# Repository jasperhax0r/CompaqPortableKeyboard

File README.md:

# Compaq Portable Keyboard — Replacement PCB, Firmware & Protocol

A drop-in replacement keyboard controller for the **Compaq Portable** (1983),
built around a Raspberry Pi Pico. It reads an 83-key diode matrix and speaks the
machine's native **IBM XT (scancode set 1)** protocol over the original 2×3
keyboard connector.

The repo also contains a **USB-serial / PS-2 test rig** used during bring-up, and
— probably the most useful part for other people — a **scope-verified writeup of
the Compaq Portable keyboard protocol**, which as far as I can tell isn't
documented anywhere else public.

Everything here is hand-solderable through-hole where possible, on purpose. The
only surface-mount parts are the two level-shifter buffers, and even those have a
through-hole alternative described in the build notes.

---

## Why this exists

The original keyboard PCBs are getting old, and the matrix routing on the
factory board is... a journey. This recreates the keyboard's electrical behavior
faithfully enough that the machine POSTs and types exactly as it did in 1983,
while letting you rebuild the board with a $15 iron and a solder sucker.

The first PCB revision is a **faithful recreation** of the original layout, on
purpose — it's a known-good reference. A rev2 with layout improvements is planned
(see `docs/rev2-notes.md`).

---

## Repository layout

```
/firmware        Pico firmware (CircuitPython)
  code.py          matrix-scan keyboard firmware (the real thing)
  test-rig/        USB-serial + PS-2 bring-up firmware
/hardware        KiCad project, schematic, PCB, Gerbers
/models          3D-printable STLs (connector keyway + fitment shims)
/tools           protocol decoder + KLE matrix-annotation scripts
  xtframe.py       decode a logic-analyzer CSV into XT scancodes
  kle_annotate.py  annotate a raw KLE layout with matrix coordinates
/docs            protocol writeup, build notes, rev2 log
```

---

## How it works

The Pico scans a **10×10 diode matrix** (83 keys, one diode per key, so full
NKRO) and emits XT scancodes on the keyboard connector.

**Power:** the Compaq feeds ~12 V down the cable. An onboard 7805 drops that to
5 V for the buffers, and the Pico runs from that 5 V into VSYS through a Schottky.
The board reproduces the original's protection: reverse-polarity Schottky, a
polyfuse, TVS clamps at the connector, and a 5.6 V crowbar across the 5 V rail.

**Level shifting:** the Pico is 3.3 V and **not** 5 V tolerant. Outbound
clock/data go through an **SN74LVC07A** (open-drain, pulled to 5 V). Inbound
reset and clock-sense come back through an **SN74LVC14A** Schmitt-trigger
cascade — the hysteresis matters, see the protocol notes on line ringing.

**Protocol:** XT scancode set 1. The keyboard generates the clock; each frame is
one start bit plus 8 data bits, LSB first, with data valid on the falling clock
edge, at roughly 24 kHz. On reset release the keyboard waits ~170 ms then sends
`0xAA` (self-test passed). Full details and scope captures in
[`docs/protocol.md`](docs/protocol.md).

---

## Building the firmware

The firmware is **CircuitPython** — no toolchain, no compile step.

1. Flash CircuitPython to the Pico.
2. Copy `firmware/code.py` to the `CIRCUITPY` drive as `code.py`.
3. That's it — it runs on boot.

### Bring-up before you install it

`code.py` has debug switches at the top:

- `DEBUG = True` prints every key make/break to the USB serial console.
- `RAW_SCAN = True` prints the raw `(row, col)` of every press, ignoring the
  keymap — use this to verify your matrix wiring against the board.
- `XT_CONNECTED = False` scans and prints but does **not** drive the XT lines,
  so you can validate the whole matrix over USB with nothing connected to the
  Compaq.

Walk every key with `RAW_SCAN = True` and confirm it matches the board before
trusting the scancode map. When it checks out, set all three back to
`DEBUG = False`, `RAW_SCAN = False`, `XT_CONNECTED = True`.

> **Note on the matrix map:** this board is wired to the *original Compaq's*
> matrix order (a straight sequential fill), **not** the interleaved mapping a
> tool like `kbplacer` produces from the KLE. If you regenerate the keymap from
> the layout file you'll get the wrong table. The map in `code.py` is the
> authoritative one — it was verified key-by-key against the physical board.

---

## Building the board

See [`docs/build.md`](docs/build.md) for the full walkthrough. The short version:

1. **Populate and verify the regulator section first.** Confirm 5.0 V at the rail
   *and* at the buffer VCC pins before any logic sees power.
2. **Power up on a current-limited bench supply** (~150 mA limit) for the first
   power-on. A wiring fault then shows as the supply hitting its limit at ~0 V,
   instead of as a hot regulator and a burn. (Ask me how I know.)
3. Then the Pico, then the level shifters, then the matrix.

The two `SN74LVC0x` buffers are TSSOP — the only fine-pitch parts. Drag-solder
with plenty of flux and wick any bridges. If you'd rather stay all-through-hole,
`docs/build.md` covers a `7407` + `CD4050B` DIP alternative (you lose the Schmitt
hysteresis on the input side, fine for a short cable).

---

## The 3D-printed parts

`/models` has the connector **keyway** (the original connector is mechanically
keyed; the print replicates that so the plug can't seat rotated — important,
since a rotated plug puts 12 V onto a signal line) and **fitment shims**.

Print in any rigid filament. PETG or ABS if it'll sit near the warm regulator;
PLA is fine otherwise.

---

## Tools

`tools/xtframe.py` decodes a logic-analyzer CSV (start bit + 8 data LSB-first,
falling-edge sampled) into XT scancodes, with a `--deglitch-us` option to reject
sub-threshold ringing on a passive tap. It was used to reverse-engineer the
protocol; it's handy for anyone probing an XT-family keyboard.

`tools/kle_annotate.py` annotates a raw [keyboard-layout-editor](https://www.keyboard-layout-editor.com)
JSON with matrix coordinates.

---

## Status

Working. The board POSTs and types on a real Compaq Portable. Known rev1
warts and the planned rev2 fixes are logged in [`docs/rev2-notes.md`](docs/rev2-notes.md)
(regulator thermal pad, hand-solder footprints, silkscreen polarity markers,
axial diode on the 5 V rail, and more).

---

## Licenses

This project is open-source hardware. Different parts carry different licenses,
because software, hardware, and documentation are legally distinct:

| Part | License |
|------|---------|
| Firmware & tools (`/firmware`, `/tools`) | **MIT** |
| Hardware & 3D models (`/hardware`, `/models`) | **CERN-OHL-S v2** |
| Documentation (`/docs`, this README) | **CC-BY-4.0** |

- The **firmware** is MIT — use it however you like.
- The **board and STL designs** are CERN-OHL-S (strongly reciprocal): if you
  make and distribute modified hardware, keep the design files open under the
  same terms.
- The **documentation and protocol writeup** are CC-BY-4.0 — reproduce and build
  on them, with attribution.

Full texts are in `/LICENSES`. See CERN-OHL-S §3 for the source-availability
requirement when distributing hardware based on this design.

---

## Acknowledgements

Original Compaq Portable schematic reference: Howard W. Sams & Co.
Computerfacts, 1987 (used for cross-referencing switch designations during
reverse engineering).

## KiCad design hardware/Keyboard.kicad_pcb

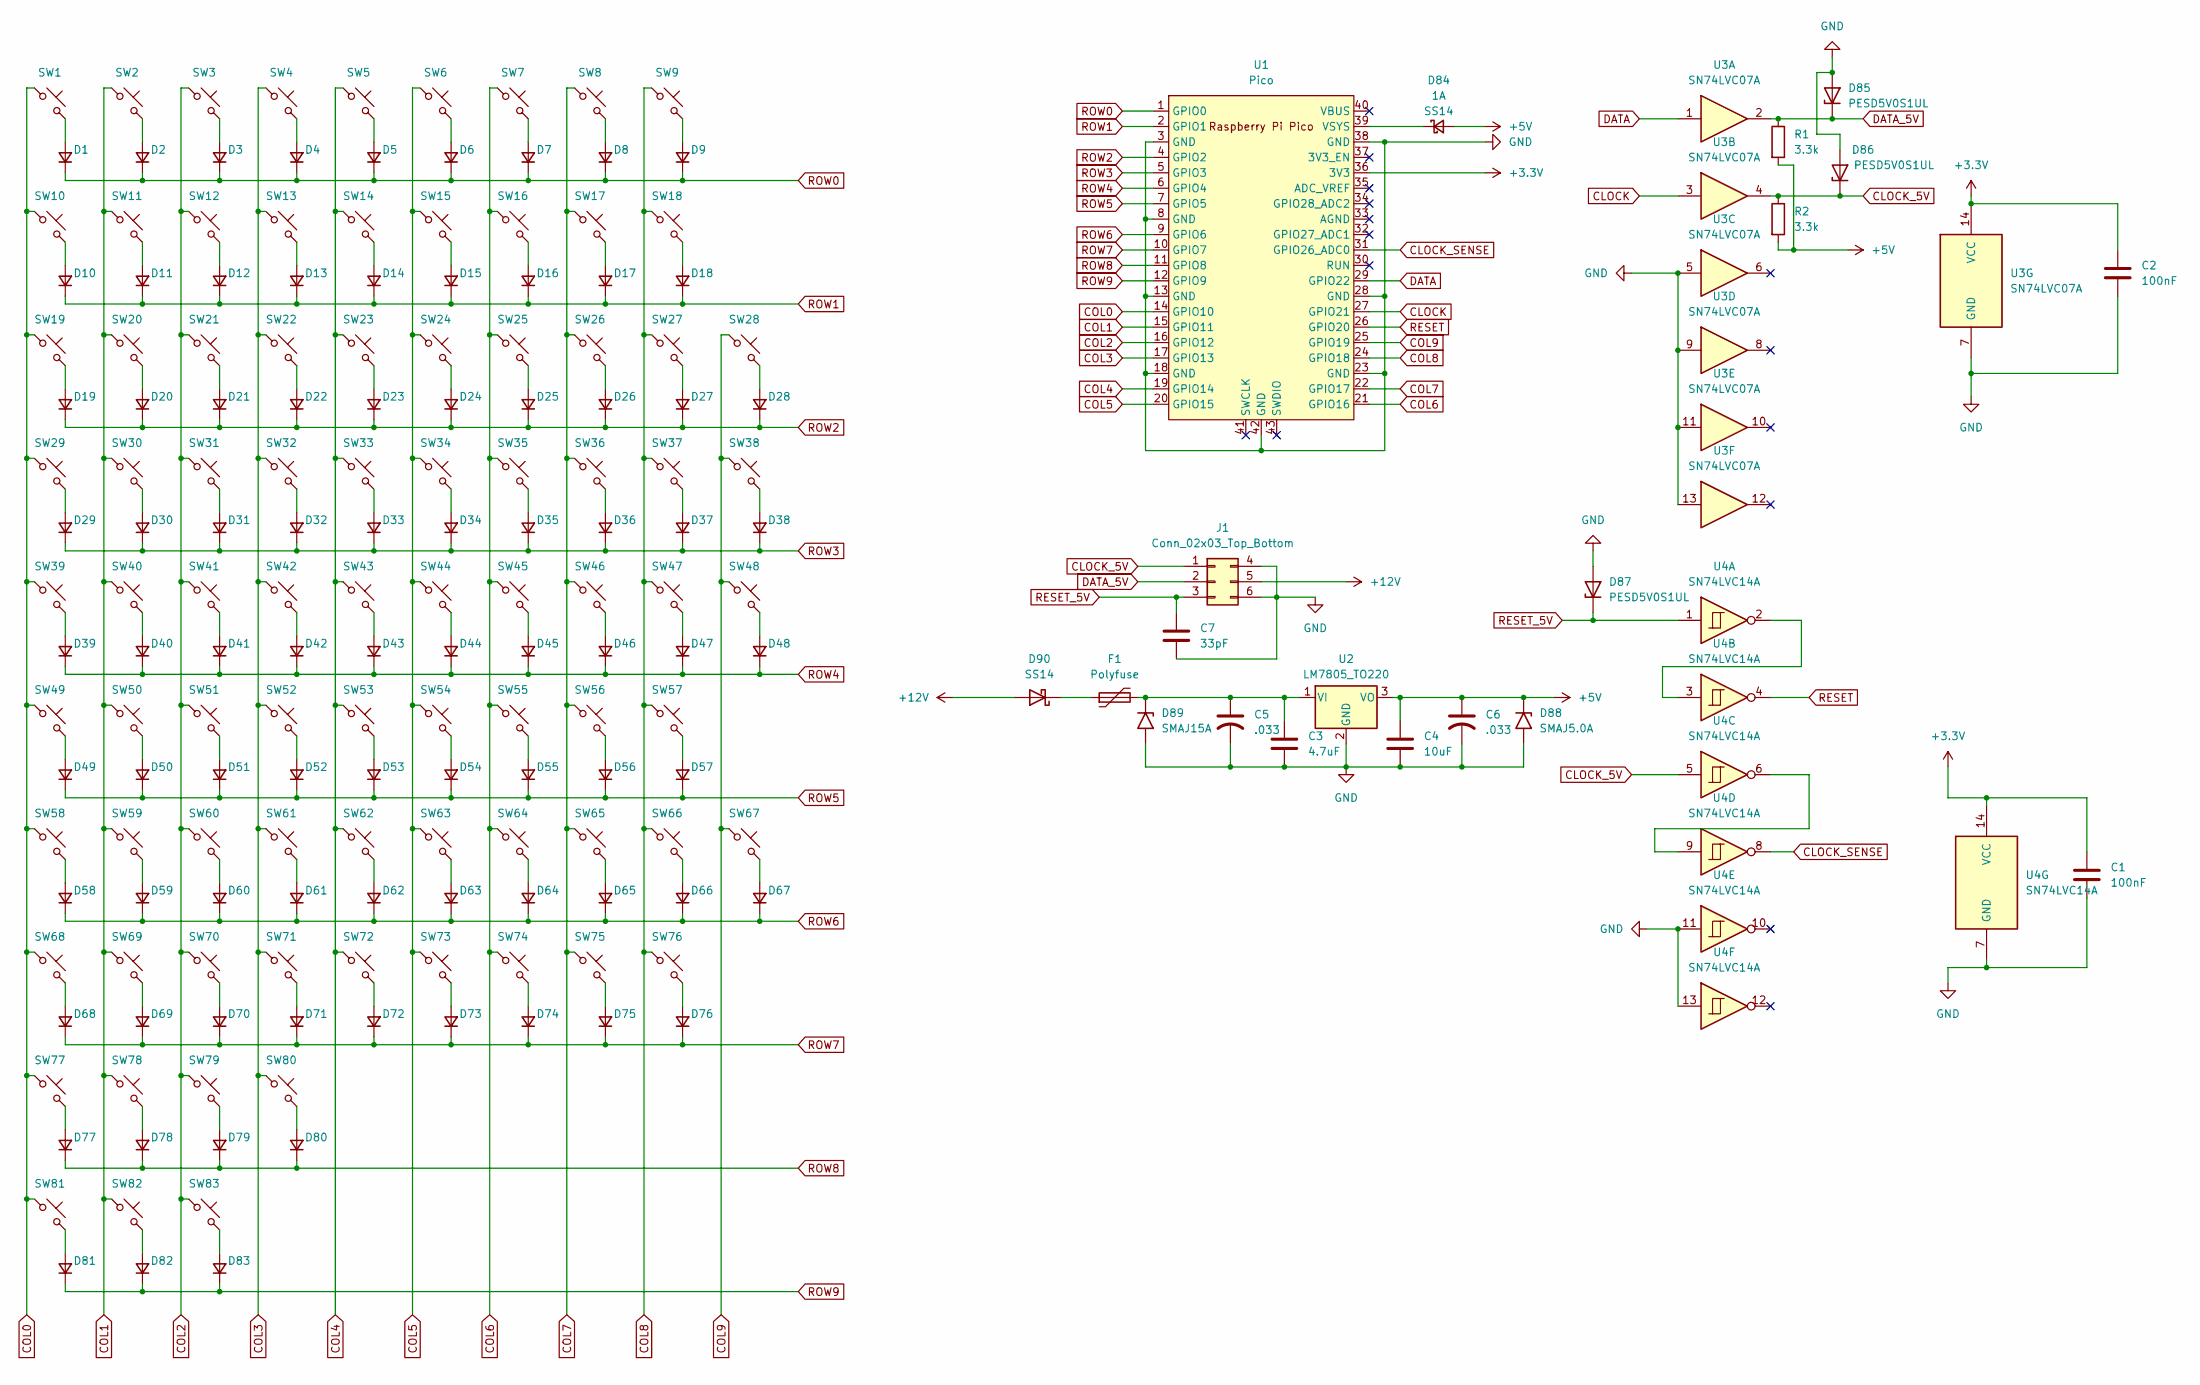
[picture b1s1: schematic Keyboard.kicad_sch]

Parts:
C1, C2: 100nF; C_Disc_D5.0mm_W2.5mm_P5.00mm
C3: 4.7uF; C_Disc_D5.0mm_W2.5mm_P5.00mm
C4: 10uF; C_Disc_D5.0mm_W2.5mm_P5.00mm
C5, C6: .033; C_Disc_D5.0mm_W2.5mm_P5.00mm
C7: 33pF; C_Disc_D5.0mm_W2.5mm_P5.00mm
D1, D2, D3, D4, D5, D6, D7, D8, D9, D10, D11, D12, D13, D14, D15, D16, D17, D18, D19, D20, D21, D22, D23, D24, D25, D26, D27, D28, D29, D30, D31, D32, D33, D34, D35, D36, D37, D38, D39, D40, D41, D42, D43, D44, D45, D46, D47, D48, D49, D50, D51, D52, D53, D54, D55, D56, D57, D58, D59, D60, D61, D62, D63, D64, D65, D66, D67, D68, D69, D70, D71, D72, D73, D74, D75, D76, D77, D78, D79, D80, D81, D82, D83: D; D_SOD-123F
D84: 1A; D_5KPW_P12.70mm_Horizontal
D85, D86, D87: PESD5V0S1UL; D_SOD-882
D88: SMAJ5.0A; D_SMA
D89: SMAJ15A; D_SMA
D90: SS14; D_SMA
F1: Polyfuse; C_Disc_D5.0mm_W2.5mm_P5.00mm
J1: Conn_02x03_Top_Bottom; PinHeader_2x03_P2.54mm_Horizontal
R1, R2: 3.3k; R_Axial_DIN0207_L6.3mm_D2.5mm_P7.62mm_Horizontal
SW1, SW2, SW3, SW4, SW5, SW6, SW7, SW8, SW9, SW10, SW11, SW12, SW13, SW14, SW15, SW16, SW17, SW18, SW19, SW20, SW21, SW22, SW23, SW24, SW25, SW26, SW27, SW28, SW29, SW30, SW31, SW32, SW33, SW34, SW35, SW36, SW37, SW38, SW39, SW40, SW41, SW42, SW43, SW44, SW45, SW46, SW47, SW48, SW49, SW50, SW51, SW52, SW53, SW54, SW55, SW56, SW57, SW58, SW59, SW60, SW61, SW62, SW63, SW64, SW65, SW66, SW67, SW68, SW69, SW70, SW71, SW72, SW73, SW74, SW75, SW76, SW77, SW78, SW79, SW81, SW82, SW83: SW_Push; SW_Cherry_MX_1.00u_PCB
SW80: SW_Push; SW_Cherry_MX_6.25u_PCB
U1: Pico; RPi_Pico_SMD_TH
U2: LM7805_TO220; TO-220-3_Vertical
U3: SN74LVC07A; TSSOP-14_4.4x5mm_P0.65mm
U4: SN74LVC14A; TSSOP-14_4.4x5mm_P0.65mm

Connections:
+3.3V: C1.1, C2.1, U1.36 (3V3), U3.14 (VCC), U4.14 (VCC)
+5V: C4.1, C6.1, D84.2 (A), D88.1 (A1), R1.2, R2.2, U2.3 (VO)
+12V: D90.2 (A), J1.5
CLOCK: U1.27 (GPIO21), U3.3
CLOCK_5V: D86.1 (K), J1.1, R2.1, U3.4, U4.5
CLOCK_SENSE: U1.31 (GPIO26_ADC0), U4.8
COL0: SW1.1, SW10.1, SW19.1, SW29.1, SW39.1, SW49.1, SW58.1, SW68.1, SW77.1, SW81.1, U1.14 (GPIO10)
COL1: SW2.1, SW11.1, SW20.1, SW30.1, SW40.1, SW50.1, SW59.1, SW69.1, SW78.1, SW82.1, U1.15 (GPIO11)
COL2: SW3.1, SW12.1, SW21.1, SW31.1, SW41.1, SW51.1, SW60.1, SW70.1, SW79.1, SW83.1, U1.16 (GPIO12)
COL3: SW4.1, SW13.1, SW22.1, SW32.1, SW42.1, SW52.1, SW61.1, SW71.1, SW80.1, U1.17 (GPIO13)
COL4: SW5.1, SW14.1, SW23.1, SW33.1, SW43.1, SW53.1, SW62.1, SW72.1, U1.19 (GPIO14)
COL5: SW6.1, SW15.1, SW24.1, SW34.1, SW44.1, SW54.1, SW63.1, SW73.1, U1.20 (GPIO15)
COL6: SW7.1, SW16.1, SW25.1, SW35.1, SW45.1, SW55.1, SW64.1, SW74.1, U1.21 (GPIO16)
COL7: SW8.1, SW17.1, SW26.1, SW36.1, SW46.1, SW56.1, SW65.1, SW75.1, U1.22 (GPIO17)
COL8: SW9.1, SW18.1, SW27.1, SW37.1, SW47.1, SW57.1, SW66.1, SW76.1, U1.24 (GPIO18)
COL9: SW28.1, SW38.1, SW48.1, SW67.1, U1.25 (GPIO19)
DATA: U1.29 (GPIO22), U3.1
DATA_5V: D85.1 (K), J1.2, R1.1, U3.2
GND: C1.2, C2.2, C3.2, C4.2, C5.2, C6.2, C7.2, D85.2 (A), D86.2 (A), D87.2 (A), D88.2 (A2), D89.2 (A2), J1.4, J1.6, U1.3 (GND), U1.8 (GND), U1.13 (GND), U1.18 (GND), U1.23 (GND), U1.28 (GND), U1.38 (GND), U1.42 (GND), U2.2 (GND), U3.5, U3.7 (GND), U3.9, U3.11, U3.13, U4.7 (GND), U4.11, U4.13
unnamed: D1.2 (A), SW1.2
unnamed: D2.2 (A), SW2.2
unnamed: D3.2 (A), SW3.2
unnamed: D4.2 (A), SW4.2
unnamed: D5.2 (A), SW5.2
unnamed: D6.2 (A), SW6.2
unnamed: D7.2 (A), SW7.2
unnamed: D8.2 (A), SW8.2
unnamed: D9.2 (A), SW9.2
unnamed: D10.2 (A), SW10.2
unnamed: D11.2 (A), SW11.2
unnamed: D12.2 (A), SW12.2
unnamed: D13.2 (A), SW13.2
unnamed: D14.2 (A), SW14.2
unnamed: D15.2 (A), SW15.2
unnamed: D16.2 (A), SW16.2
unnamed: D17.2 (A), SW17.2
unnamed: D18.2 (A), SW18.2
unnamed: D19.2 (A), SW19.2
unnamed: D20.2 (A), SW20.2
unnamed: D21.2 (A), SW21.2
unnamed: D22.2 (A), SW22.2
unnamed: D23.2 (A), SW23.2
unnamed: D24.2 (A), SW24.2
unnamed: D25.2 (A), SW25.2
unnamed: D26.2 (A), SW26.2
unnamed: D27.2 (A), SW27.2
unnamed: D28.2 (A), SW28.2
unnamed: D29.2 (A), SW29.2
unnamed: D30.2 (A), SW30.2
unnamed: D31.2 (A), SW31.2
unnamed: D32.2 (A), SW32.2
unnamed: D33.2 (A), SW33.2
unnamed: D34.2 (A), SW34.2
unnamed: D35.2 (A), SW35.2
unnamed: D36.2 (A), SW36.2
unnamed: D37.2 (A), SW37.2
unnamed: D38.2 (A), SW38.2
unnamed: D39.2 (A), SW39.2
unnamed: D40.2 (A), SW40.2
unnamed: D41.2 (A), SW41.2
unnamed: D42.2 (A), SW42.2
unnamed: D43.2 (A), SW43.2
unnamed: D44.2 (A), SW44.2
unnamed: D45.2 (A), SW45.2
unnamed: D46.2 (A), SW46.2
unnamed: D47.2 (A), SW47.2
unnamed: D48.2 (A), SW48.2
unnamed: D49.2 (A), SW49.2
unnamed: D50.2 (A), SW50.2
unnamed: D51.2 (A), SW51.2
unnamed: D52.2 (A), SW52.2
unnamed: D53.2 (A), SW53.2
unnamed: D54.2 (A), SW54.2
unnamed: D55.2 (A), SW55.2
unnamed: D56.2 (A), SW56.2
unnamed: D57.2 (A), SW57.2
unnamed: D58.2 (A), SW58.2
unnamed: D59.2 (A), SW59.2
unnamed: D60.2 (A), SW60.2
unnamed: D61.2 (A), SW61.2
unnamed: D62.2 (A), SW62.2
unnamed: D63.2 (A), SW63.2
unnamed: D64.2 (A), SW64.2
unnamed: D65.2 (A), SW65.2
unnamed: D66.2 (A), SW66.2
unnamed: D67.2 (A), SW67.2
unnamed: D68.2 (A), SW68.2
unnamed: D69.2 (A), SW69.2
unnamed: D70.2 (A), SW70.2
unnamed: D71.2 (A), SW71.2
unnamed: D72.2 (A), SW72.2
unnamed: D73.2 (A), SW73.2
unnamed: D74.2 (A), SW74.2
unnamed: D75.2 (A), SW75.2
unnamed: D76.2 (A), SW76.2
unnamed: D77.2 (A), SW77.2
unnamed: D78.2 (A), SW78.2
unnamed: D79.2 (A), SW79.2
unnamed: D80.2 (A), SW80.2
unnamed: D81.2 (A), SW81.2
unnamed: D82.2 (A), SW82.2
unnamed: D83.2 (A), SW83.2
unnamed: D84.1 (K), U1.39 (VSYS)
unnamed: C3.1, C5.1, D89.1 (A1), F1.2, U2.1 (VI)
unnamed: D90.1 (K), F1.1
unnamed: U4.2, U4.3
unnamed: U4.6, U4.9
RESET: U1.26 (GPIO20), U4.4
RESET_5V: C7.1, D87.1 (K), J1.3, U4.1
ROW0: D1.1 (K), D2.1 (K), D3.1 (K), D4.1 (K), D5.1 (K), D6.1 (K), D7.1 (K), D8.1 (K), D9.1 (K), U1.1 (GPIO0)
ROW1: D10.1 (K), D11.1 (K), D12.1 (K), D13.1 (K), D14.1 (K), D15.1 (K), D16.1 (K), D17.1 (K), D18.1 (K), U1.2 (GPIO1)
ROW2: D19.1 (K), D20.1 (K), D21.1 (K), D22.1 (K), D23.1 (K), D24.1 (K), D25.1 (K), D26.1 (K), D27.1 (K), D28.1 (K), U1.4 (GPIO2)
ROW3: D29.1 (K), D30.1 (K), D31.1 (K), D32.1 (K), D33.1 (K), D34.1 (K), D35.1 (K), D36.1 (K), D37.1 (K), D38.1 (K), U1.5 (GPIO3)
ROW4: D39.1 (K), D40.1 (K), D41.1 (K), D42.1 (K), D43.1 (K), D44.1 (K), D45.1 (K), D46.1 (K), D47.1 (K), D48.1 (K), U1.6 (GPIO4)
ROW5: D49.1 (K), D50.1 (K), D51.1 (K), D52.1 (K), D53.1 (K), D54.1 (K), D55.1 (K), D56.1 (K), D57.1 (K), U1.7 (GPIO5)
ROW6: D58.1 (K), D59.1 (K), D60.1 (K), D61.1 (K), D62.1 (K), D63.1 (K), D64.1 (K), D65.1 (K), D66.1 (K), D67.1 (K), U1.9 (GPIO6)
ROW7: D68.1 (K), D69.1 (K), D70.1 (K), D71.1 (K), D72.1 (K), D73.1 (K), D74.1 (K), D75.1 (K), D76.1 (K), U1.10 (GPIO7)
ROW8: D77.1 (K), D78.1 (K), D79.1 (K), D80.1 (K), U1.11 (GPIO8)
ROW9: D81.1 (K), D82.1 (K), D83.1 (K), U1.12 (GPIO9)

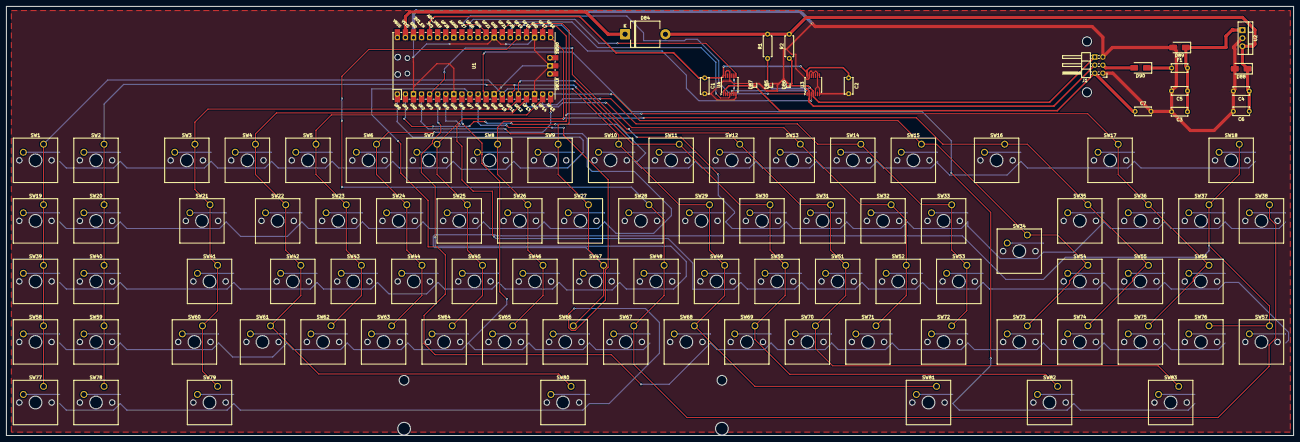
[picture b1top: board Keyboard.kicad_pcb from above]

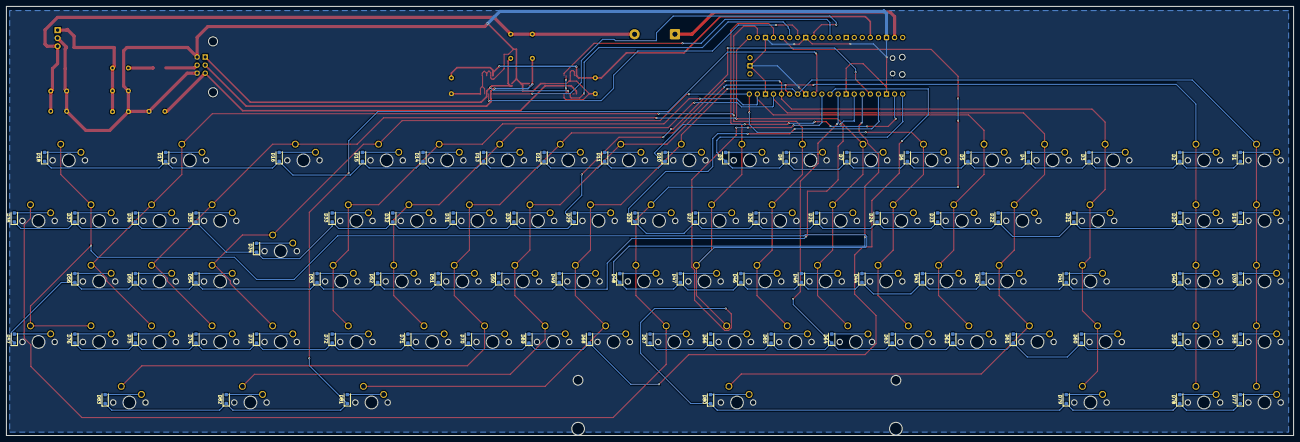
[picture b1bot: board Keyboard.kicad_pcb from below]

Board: 2 copper layers, 405.0 x 135.0 mm, 188 parts (83 on the bottom side), 119 nets.
